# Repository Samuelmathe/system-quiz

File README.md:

# DMX Quiz Project (Arduino + Python)

Ce dossier contient :
- des **sketches Arduino** (`.ino`)
- 2 **logiciels Python** (interfaces GUI) pour piloter/configurer le système via USB (port série)

## Contenu

- **Arduino**
  - `megaf.ino` : sketch pour Arduino MEGA (DMX + logique de jeu ; plus de radio directe, voir `rf_nano_bridge.ino`)
  - `rf_nano_bridge.ino` : sketch pour **RF-Nano** (Nano + nRF24 intégrés) — pont radio nRF24 ↔ série vers le Mega ; seule carte du système avec un module radio
  - `buzzer_nano_equipe.ino` : sketch pour Arduino NANO (équipe)
  - `nano_son_final.ino` : sketch pour Arduino NANO (son)
  - `nano_animateur_final.ino` : sketch pour Arduino NANO (animateur)

- **Python**
  - `configuration/config_final_30.py` : outil de configuration (équipes / DMX / sync MEGA)
  - `interface/interface_30eq.py` : interface “quiz board” (scores/buzz + série)
  - `diagnostics/quiz_logger.py` : logger de diagnostic (écoute passive d'un port série dédié, en parallèle du logiciel de score — voir [Diagnostics](#diagnostics-quiz_loggerpy))

**Modes d’utilisation (sans PC / PC+Mega / PC+nano son)** : voir [MODES.md](MODES.md).

## Prérequis

- Python 3.9+ recommandé
- Arduino IDE (ou PlatformIO) pour compiler/téléverser les `.ino`

## Installation Python

Depuis la racine du projet :

```bash
python3 -m pip install --user -r requirements.txt
```

## Lancer les logiciels Python

Depuis la racine du projet :

```bash
python3 configuration/config_final_30.py
python3 interface/interface_30eq.py
```

## Fichiers créés automatiquement (configs)

- `configuration/config_final_30.py` lit/écrit : `configuration/config_quiz_pro.json`
- `interface/interface_30eq.py` lit/écrit : `interface/quiz_board_config.json`

Ces fichiers JSON sont créés automatiquement **à côté de chaque script**, ce qui rend le projet plus simple à partager et lancer depuis n'importe quel dossier.

## Sons (interface)

`interface/interface_30eq.py` essaie de charger des sons depuis le dossier `sounds/` **à côté du script** :
- `buzz.mp3` (buzz général / fallback)
- `victoire.mp3` (bonne réponse)
- `echec.mp3` (mauvaise réponse)
- `equipe_1.mp3` → `equipe_30.mp3` (sons spécifiques par équipe, optionnels)

Le dossier `sounds/` doit être **à côté du script** (ou à côté de l’exécutable si tu as “packagé” l’app).
Exemple attendu :

```
interface/
  interface_30eq.py
  sounds/
    buzz.mp3
    victoire.mp3
    echec.mp3
    equipe_1.mp3
    ...
    equipe_30.mp3
```

Si `pygame` n’est pas dispo (ou si les fichiers sont absents), l’interface fonctionne, mais sans sons.

## Diagnostics (`quiz_logger.py`)

Outil séparé du logiciel de score : il écoute en **passif** un port série de diagnostic
(un adaptateur USB-TTL dédié, branché en parallèle sur `PC_SERIAL`/`Serial3` du Mega —
aucun conflit avec le logiciel de score, qui utilise son propre adaptateur).

Il affiche le flux en direct, enregistre le log complet dans un fichier horodaté, et
génère un fichier résumé (durée de session, nombre de buzz, freezes/silences détectés,
redémarrages Mega détectés) pratique à partager pour du support/diagnostic à distance.

```bash
python3 diagnostics/quiz_logger.py
```

Un exécutable Windows est aussi généré automatiquement par GitHub Actions à chaque
modification de ce fichier (voir l'onglet *Actions* du dépôt).

## Linux : accès au port série Arduino

Si tu as une erreur de permission sur `/dev/ttyACM0` ou `/dev/ttyUSB0` :

```bash
sudo usermod -aG dialout $USER
```

Puis **déconnexion/reconnexion** (ou redémarrage) pour que le groupe soit pris en compte.

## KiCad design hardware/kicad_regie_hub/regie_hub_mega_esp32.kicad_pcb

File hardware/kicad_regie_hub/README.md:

# Schéma de départ — Régie/Hub (adaptateur Mega + ESP32 + nRF24)

`regie_hub_mega_esp32.kicad_sch` : même méthode que les deux cartes buzzer (généré, **vérifié avec `kicad-cli sch erc` réel**). 11 composants, 14 nets.

## ⚠️ Correction : broches VCC/GND du nRF24 inversées, module PA+LNA (2×4)

Même correction que sur la carte buzzer Nano (voir `../kicad_buzzer_nano/README.md` pour le détail complet) : **J_NRF avait VCC en broche 1 et GND en broche 2 — inversé par rapport à la vraie numérotation** (broche 1 = GND, broche 2 = VCC), vérifié contre 3 sources indépendantes. Corrigé partout. Ton module confirmé étant un **nRF24L01+PA+LNA** (2×4 broches), l'empreinte J_NRF est passée de `PinSocket_1x08` à `PinHeader_2x04` (connecteur **mâle** — le module a lui-même des ports femelles, donc c'est la carte qui doit porter les broches mâles).

## Ce que cette carte est (et n'est pas)

**Ce n'est PAS un shield Mega complet.** Le shield DMX (`quizkicad/mega`, projet séparé, non touché) s'empile déjà directement sur la Mega. Cette carte-ci est un **petit adaptateur** qui porte l'ESP32 + le nRF24 + l'électronique entre les deux, relié à la Mega par seulement **6 fils** :

| Broche J_MEGA | Signal | Vers la Mega |
|---|---|---|
| 1 | TX2 (5V) | Mega pin 16 |
| 2 | RX2 | Mega pin 17 |
| 3 | TX1 (5V) | Mega pin 18 |
| 4 | RX1 | Mega pin 19 |
| 5 | 5V | Sortie régulateur onboard de la Mega |
| 6 | GND | Masse commune |

⚠️ **[FIX] Broches 3/4 déplacées de Mega Serial3 (pins 14/15) vers Mega Serial1 (pins 18/19)** : en vérifiant le câblage réel avec Samuel, Serial3 était déjà utilisé par le shield DMX (mal aiguillé côté firmware, corrigé dans `megaf.ino`) et doit rester dédié au câble TTL PC (scripts Python) comme lien de secours simultané au WiFi. Serial1 était complètement libre sur la Mega — voir `megaf.ino` et `esp32/esp32_bridge_server.ino` pour le détail complet.

**Alimentation** : pas de batterie sur cette carte — confirmé par toi : "on branche le mega [secteur] mais le reste des modules sera alimenté [par lui]". Le 5V vient du régulateur déjà présent sur la Mega.

## Pourquoi un pont diviseur et pas un module convertisseur de niveau logique

Tu as mentionné un "convertisseur logique" entre les RX/TX de la Mega et de l'ESP32. J'ai utilisé le **pont diviseur 1kΩ/2kΩ** à la place d'un module dédié — ce n'est pas un raccourci, c'est la solution **déjà documentée et déjà validée sur ce projet** (`cl.md` section 3.3, schéma dans `docs/APK_HYBRIDE_GUIDE.md`) pour exactement ces deux liaisons série. Réutiliser une solution qui marche déjà coûte moins cher et évite d'introduire une dépendance à un nouveau module non testé sur ce projet.

- **R1/R2** : diviseur sur Mega TX2 (5V) → ESP32 RX1 (3,3V) — lien Jeu.
- **R3/R4** : diviseur sur Mega TX1 (5V) → ESP32 RX2 (3,3V) — lien Config EEPROM (déplacé depuis TX3, voir note ci-dessus).
- **Pas de diviseur dans l'autre sens** (ESP32 TX → Mega RX) : déjà documenté que le 3,3V est lu comme HIGH par les entrées 5V de la Mega, connexion directe.

## Pourquoi un régulateur dédié au nRF24 (pas le 3V3 de l'ESP32)

Demandé : "un régulateur pour esp32" + "tout ce qui va avec ces composants pour un meilleur rendement". Plutôt que d'alimenter le nRF24 depuis la broche 3V3 embarquée de l'ESP32 (qui partage déjà la charge du Wi-Fi — creux de tension possible, cause connue d'instabilité nRF24, historique documenté sur ce projet), **U_REG** est un module régulateur 3,3V dédié rien que pour le nRF24, avec son propre découplage (C2, C3 — le condensateur 10-100µF déjà exigé par `cl.md` pour le nRF24).

## Avertissements ERC (36 au total)

Même profil que les deux cartes buzzer, déjà expliqué en détail dans `../kicad_buzzer_nano/README.md` — normal en pratique KiCad (comparé contre `quizkicad/mega`, ton propre projet fait à la main) :

| Type | Nombre | Normal ? |
|---|---|---|
| `endpoint_off_grid` | 20 | Cosmétique |
| `lib_symbol_mismatch` | 9 | Cosmétique — `Outils > Mettre à jour les symboles depuis la bibliothèque` |
| `pin_not_connected` | 4 | 2 attendus (3V3 onboard ESP32 et IRQ nRF24, non utilisés — no-connect posé), 2 liés au réseau GND (nuance ERC normale, voir README buzzer) |
| `no_connect_dangling` | 2 | Marqueurs "pas de connexion" légèrement décalés — à recaler d'un clic |
| `power_pin_not_driven` | 1 | Normal sur un réseau GND (également présent dans `quizkicad/mega`) |

## PCB : placement compact + pistes routées

`regie_hub_mega_esp32.kicad_pcb` : empreintes placées, **et pistes routées** — même pipeline que les deux cartes buzzer (Freerouting en CLI headless + réimport KiCad + `kicad-cli pcb drc` réel), voir `../kicad_buzzer_nano/README.md` pour le détail (y compris le mécanisme de keepout, identique ici).

**Changements suite à ta relecture** :
- **Le texte-guide en sérigraphie a été retiré** — repères de composants standards uniquement (J_MEGA, U_ESP32L/R, J_NRF, U_REG, R1-R4, C1-C3), pas de paragraphe d'instructions gravé sur la carte.
- **Carte bien plus compacte** : ~137×85mm au lieu de 185×145mm.
- **C3 (découplage nRF24) encore rapproché de J_NRF** (~12mm, contre 25mm dans la toute première version).
- **Zone sans cuivre sous le nRF24** : même mécanisme keepout que la carte Nano (voir son README pour le détail de la vérification), placé en presqu'île contre le bord droit pour ne bloquer aucun chemin de routage.
- **U_ESP32 est un vrai port femelle** : deux barrettes `PinSocket_1x15` (U_ESP32L/R, 30 broches, entraxe 15,24mm). Seules 11 des 30 positions physiques sont câblées ; les 19 autres sont présentes pour que le module s'enfiche mécaniquement. Brochage : **DOIT ESP32 DevKit V1, 30 broches** — exactement le modèle confirmé commandé, design de référence unique et bien plus standardisé que les clones 38 broches (vérifié sur https://www.espboards.dev/esp32/esp32doit-devkit-v1/).
- **J_NRF (nRF24) est un connecteur MÂLE 2×4** (`PinHeader_2x04`) — le module a des ports femelles dessus, donc la carte porte les broches mâles. 1=GND, 2=VCC, puis CE/CSN/SCK/MOSI/MISO/IRQ. ⚠️ **Vérifie les repères sur ton module avant de souder**, aucun standard universel pour les variantes PA+LNA.
- **R1-R4 et C1-C3 sont maintenant en CMS** (`R_0805`/`C_0805`), par choix explicite pour un assemblage machine (PCBA) chez le fabricant. Même numérotation de broche qu'avant. **Restent traversants** : J_MEGA, U_ESP32L/R et J_NRF (connecteurs de liaison/modules enfichables, pas adaptés au CMS).
- Aperçu : `apercu_pcb.png`.

**Résultat** : 78 connexions (14 nets), **0 violation de clearance, 0 élément non connecté**, 5 vias placées, keepout respecté (0 piste dedans, vérifié par script). DRC final : 12 avertissements, tous `lib_footprint_mismatch` (cosmétique). 4 `track_dangling` initiaux (résidus d'autorouter) identifiés et supprimés après vérification de la topologie réelle — **0 track_dangling restant**.

**C3 (découplage nRF24) rapproché de J_NRF** : le placement initial mettait C3 à 25mm de J_NRF (net `NRF_VCC_DEDIE`, qui relie aussi C2 et U_REG — ce n'est pas un simple lien à 2 broches). Trop loin pour un découplage propre à 2,4GHz. C3 a été repositionné à 12mm de J_NRF (`(152,20)` au lieu de `(165,20)`) et la carte entièrement re-routée : la piste J_NRF↔C3 est maintenant un tronçon direct et court, visible sur `apercu_pcb.png`.

## Prochaine étape

Ouvre le PCB dans KiCad et relis le routage à l'œil, puis passe aux fichiers de fabrication (Gerbers) — en particulier bien respecter les recommandations `cl.md` (VCC nRF24 en 3,3V uniquement jamais 5V, GND commun).

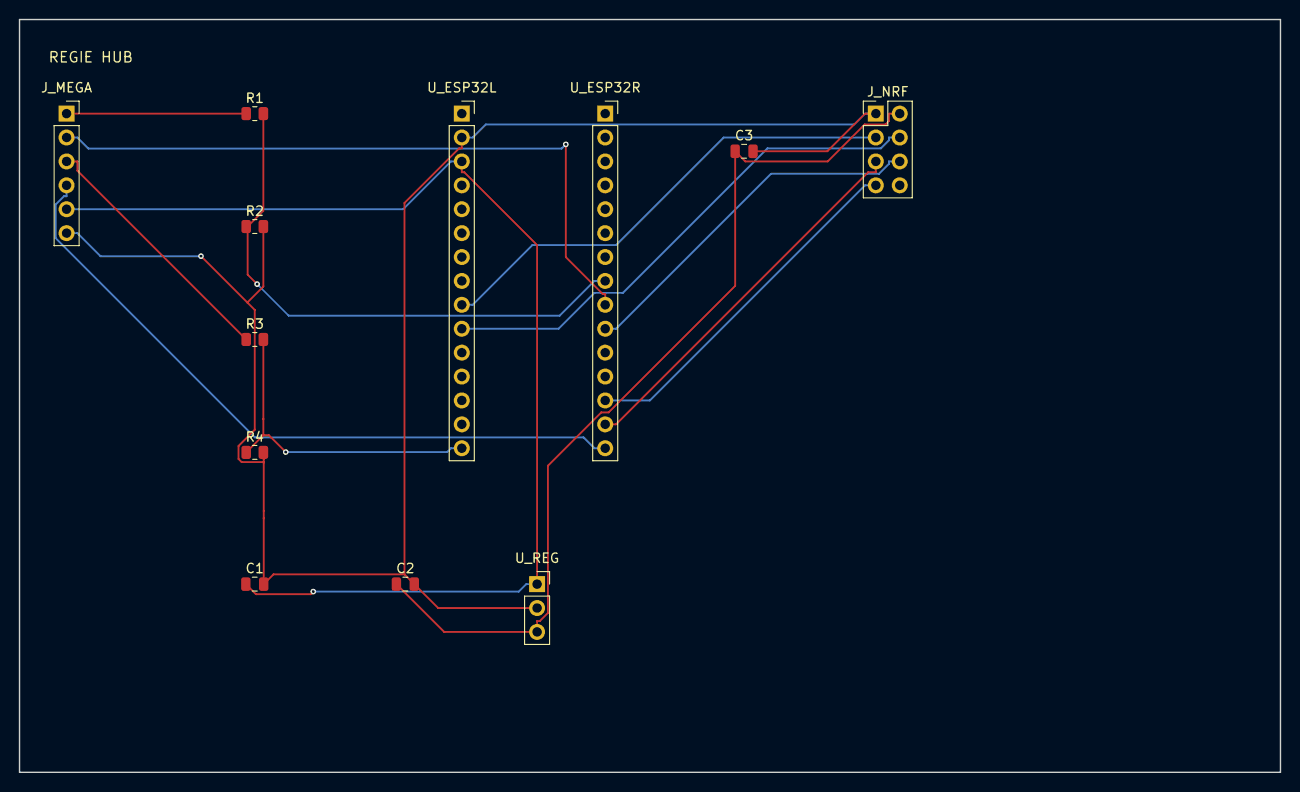
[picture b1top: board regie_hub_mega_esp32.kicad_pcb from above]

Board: 2 copper layers, 134.0 x 80.0 mm, 12 parts (0 on the bottom side), 14 nets.

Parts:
C1: ~10uF decouplage entree regulateur - CMS; C_0805_2012Metric
C2: ~10uF decouplage sortie regulateur - CMS; C_0805_2012Metric
C3: 10-100uF decouplage nRF24 (obligatoire, au plus p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; C_0805_2012Metric
J_MEGA: Vers Mega: TX2(16) RX2(17) TX1(18) RX1(19) 5V GND; PinSocket_1x06_P2.54mm_Vertical
J_NRF: nRF24L01+PA+LNA (broches MALES, le module a des p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; PinHeader_2x04_P2.54mm_Vertical
R1: 1k (diviseur TX2, serie) - CMS; R_0805_2012Metric
R2: 2k (diviseur TX2, vers GND) - CMS; R_0805_2012Metric
R3: 1k (diviseur TX3, serie) - CMS; R_0805_2012Metric
R4: 2k (diviseur TX3, vers GND) - CMS; R_0805_2012Metric
U_ESP32L: ESP32 DevKit V1 colonne gauche (broches 1-15); PinSocket_1x15_P2.54mm_Vertical
U_ESP32R: ESP32 DevKit V1 colonne droite (broches 16-30); PinSocket_1x15_P2.54mm_Vertical
U_REG: Regulateur 3.3V dedie (ex AMS1117-3.3); PinSocket_1x03_P2.54mm_Vertical

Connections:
ESP32_RX1_3V3: R1.2, R2.1, U_ESP32R.23
ESP32_RX2_3V3: R3.2, R4.1, U_ESP32L.15
GND: C1.2, C2.2, C3.2, J_MEGA.6, J_NRF.1, R2.2, R4.2, U_ESP32L.2, U_REG.2
MEGA_RX2_DIRECT: J_MEGA.2, U_ESP32R.22
MEGA_RX3_DIRECT: J_MEGA.4, U_ESP32R.16
MEGA_TX2_5V: J_MEGA.1, R1.1
MEGA_TX3_5V: J_MEGA.3, R3.1
NRF_CE: J_NRF.3, U_ESP32L.9
NRF_CSN: J_NRF.4, U_ESP32L.10
NRF_MISO: J_NRF.7, U_ESP32R.18
NRF_MOSI: J_NRF.6, U_ESP32R.21
NRF_SCK: J_NRF.5, U_ESP32R.17
NRF_VCC_DEDIE: C2.1, C3.1, J_NRF.2, U_REG.3
VCC_5V_MEGA: C1.1, J_MEGA.5, U_ESP32L.3, U_REG.1

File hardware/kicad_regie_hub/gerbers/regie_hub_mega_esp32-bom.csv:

Designator,Comment,Footprint
C1,~10uF decouplage entree regulateur - CMS,Capacitor_SMD:C_0805_2012Metric
C2,~10uF decouplage sortie regulateur - CMS,Capacitor_SMD:C_0805_2012Metric
C3,"10-100uF decouplage nRF24 (obligatoire, au plus pres) - CMS",Capacitor_SMD:C_0805_2012Metric
J_MEGA,Vers Mega: TX2 RX2 TX3 RX3 5V GND,Connector_PinSocket_2.54mm:PinSocket_1x06_P2.54mm_Vertical
J_NRF,"nRF24L01+PA+LNA (broches MALES, le module a des ports femelles) - VERIFIER le brochage sur le module recu",Connector_PinHeader_2.54mm:PinHeader_2x04_P2.54mm_Vertical
R1,"1k (diviseur TX2, serie) - CMS",Resistor_SMD:R_0805_2012Metric
R2,"2k (diviseur TX2, vers GND) - CMS",Resistor_SMD:R_0805_2012Metric
R3,"1k (diviseur TX3, serie) - CMS",Resistor_SMD:R_0805_2012Metric
R4,"2k (diviseur TX3, vers GND) - CMS",Resistor_SMD:R_0805_2012Metric
U_ESP32L,ESP32 DevKit V1 colonne gauche (broches 1-15),Connector_PinSocket_2.54mm:PinSocket_1x15_P2.54mm_Vertical
U_ESP32R,ESP32 DevKit V1 colonne droite (broches 16-30),Connector_PinSocket_2.54mm:PinSocket_1x15_P2.54mm_Vertical
U_REG,Regulateur 3.3V dedie (ex AMS1117-3.3),Connector_PinSocket_2.54mm:PinSocket_1x03_P2.54mm_Vertical

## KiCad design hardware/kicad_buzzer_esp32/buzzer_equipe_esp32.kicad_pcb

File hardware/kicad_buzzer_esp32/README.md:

# Schéma de départ — Buzzer équipe (secours ESP32 / ESP-NOW)

`buzzer_equipe_esp32.kicad_sch` : même méthode que `../kicad_buzzer_nano/` (généré à partir du BOM, vérifié avec `kicad-cli sch erc` réel). 6 composants, 6 nets.

## L'ESP32 est représenté comme un connecteur générique 4 broches

Il n'existe pas de symbole KiCad standard pour la carte exacte commandée (ESP32 DevKit V1/ESP32-DevKitC-32 — trop de variantes de brochage différentes selon les fabricants). **U1** représente donc uniquement les 4 signaux réellement câblés sur ce PCB vers le module ESP32, pas les ~30 broches physiques :

| Broche U1 | Signal ESP32 | Usage (voir `esp32_buzzer_equipe.ino`) |
|---|---|---|
| 1 | GPIO4 | Bouton buzz |
| 2 | GPIO13 | IN du module vibreur |
| 3 | 5V / VIN | Alimentation |
| 4 | GND | Masse |

GPIO2 (LED embarquée) n'apparaît pas : elle est **interne au module ESP32 lui-même**, rien à router sur ce PCB pour elle.

## Avertissements ERC (28 au total)

| Type | Nombre | Normal ? |
|---|---|---|
| `endpoint_off_grid` | 12 | Cosmétique, sans conséquence électrique |
| `pin_not_connected` | 7 | À vérifier une fois dans l'interface — voir note ci-dessous |
| `lib_symbol_mismatch` | 7 | Cosmétique — `Outils > Mettre à jour les symboles depuis la bibliothèque` |
| `label_dangling` | 1 | **Normal en pratique** — ton propre projet `quizkicad/mega` (fait à la main) en a **71** du même genre. Pas un signe d'erreur de génération. |
| `power_pin_not_driven` | 1 | **Normal en pratique** — présent aussi dans `quizkicad/mega` (3 occurrences). |

Le `label_dangling` et plusieurs `pin_not_connected` concernent le réseau `BAT_PLUS`/`GND` autour de `BT1`/`J2`/`U1` — les coordonnées calculées correspondent bien aux broches réelles (vérifié), mais KiCad les affiche quand même comme non connectés. Comme pour la version Nano : cliquez l'étiquette et redéplacez-la légèrement pour forcer la reconnexion visuelle, ou ignorez si vous câblez de toute façon ce réseau en dur au routage du PCB.

## Rappel important

`ESPNOW_WIFI_CHANNEL` dans `esp32_buzzer_equipe.ino` doit rester identique à celui du hub (`esp32/esp32_bridge_server.ino`) — sans rapport avec ce schéma, mais à ne pas oublier au premier flash de la carte.

## PCB : placement compact + pistes routées

`buzzer_equipe_esp32.kicad_pcb` : empreintes placées, **et pistes routées** — même pipeline que la carte Nano (Freerouting en CLI headless + réimport KiCad + `kicad-cli pcb drc` réel), voir `../kicad_buzzer_nano/README.md` pour le détail du pipeline.

**Changements suite à ta relecture** :
- **Le texte-guide en sérigraphie a été retiré** — repères de composants standards uniquement (U1L, U1R, SW1...).
- **Carte bien plus compacte** : ~68×101mm au lieu de 130×145mm.
- **v3 : réduite encore à 65×50mm exactement**, pour correspondre au boîtier déjà conçu. U1L/U1R (les deux barrettes du module ESP32, 49mm de long chacune) ont dû être **pivotées à 90°** pour tenir dans cette largeur — leur entraxe réel (22,86mm) est inchangé, seule l'orientation sur la carte change, ça ne modifie rien au câblage ni au module qui s'enfiche dessus. Les 6 petits connecteurs (SW1, SW2, BATLED, J3, J2, BT1) sont serrés sur une seule rangée en bas de la carte, J2/J3 également pivotés à 90° pour gagner de la place en hauteur.
- Pas de keepout sur cette carte : pas de nRF24 ici, l'ESP-NOW utilise l'antenne intégrée à la puce ESP32 elle-même.
- **SW1, SW2, J2, J3 (connecteurs "fils volants") sont maintenant en CMS** (empreintes SMD), par choix explicite pour un assemblage machine (PCBA) chez le fabricant. Même numérotation de broche qu'avant. **Restent traversants** : U1L/U1R (le module ESP32 s'enfiche dessus) et **BT1**.
- **BT1 (batterie) est un vrai connecteur JST-PH** (`JST_PH_B2B-PH-K`, mâle, traversant) — même raisonnement que la carte Nano (voir son README) : la batterie a déjà une prise femelle sertie sur ses fils, et ce connecteur encaisse des cycles de branchement/débranchement qu'un pad CMS ne supporterait pas. Broche 1 = + (rouge), broche 2 = − (noir) — **vérifie la polarité sur ta batterie reçue**.
- **Nouveau : BATLED**, connecteur 2 broches (CMS) pour le module indicateur de niveau de batterie (4 LED) — même composant/câblage que la carte Nano, voir son README pour le détail.

**U1 est un vrai port femelle** : deux barrettes `PinSocket_1x19` (U1L/U1R, 38 broches au total, entraxe 22,86mm — la dimension déjà notée dans `hardware/boitier_buzzer_equipe.scad` pour ce module). Seules 4 des 38 positions physiques sont câblées (GPIO4, GPIO13, VIN, GND) ; les 34 autres sont présentes uniquement pour que le module s'enfiche mécaniquement.

⚠️ **Brochage à vérifier sur le module reçu avant de souder** : contrairement à la carte hub (ESP32 DevKit V1 30 broches, un modèle de référence unique et confirmé par toi), les cartes ESP32 38 broches existent en plusieurs variantes de brochage chez différents fabricants. J'ai utilisé la disposition générique la plus courante ("style NodeMCU-32S", vérifiée sur https://www.espboards.dev/esp32/esp32-38pin-devkit-generic/) : broche réelle 32 = GPIO4, broche 15 = GPIO13, broche 19 = VIN, broche 14 = GND. **Compare ces numéros avec les repères imprimés sur ton module avant de souder** — si ça ne correspond pas, il suffit de déplacer les 4 fils, la carte elle-même n'a pas besoin d'être refaite.

- Aperçu : `apercu_pcb.png`.

**Résultat (v3, 65×50mm)** : **0 violation de clearance, 0 élément non connecté**. DRC final : 19 avertissements, tous cosmétiques — `lib_footprint_mismatch` (5, comme d'habitude), `silk_overlap` (1, texte de référence U1R qui chevauche légèrement son propre contour après la rotation à 90°), et `silk_over_copper` (13, des pistes routées passent juste sous la sérigraphie de J2/J3 — carte très dense, aucun impact électrique, juste un risque que l'encre sérigraphie ne s'imprime pas parfaitement à ces endroits précis). Un `track_dangling` initial (résidu d'autorouter, un stub B.Cu redondant en doublon d'un chemin déjà assuré côté F.Cu) identifié et supprimé après vérification de la topologie réelle — **0 track_dangling restant**.

## Prochaine étape

Ouvre le PCB dans KiCad, relis le routage à l'œil, puis passe aux fichiers de fabrication (Gerbers).

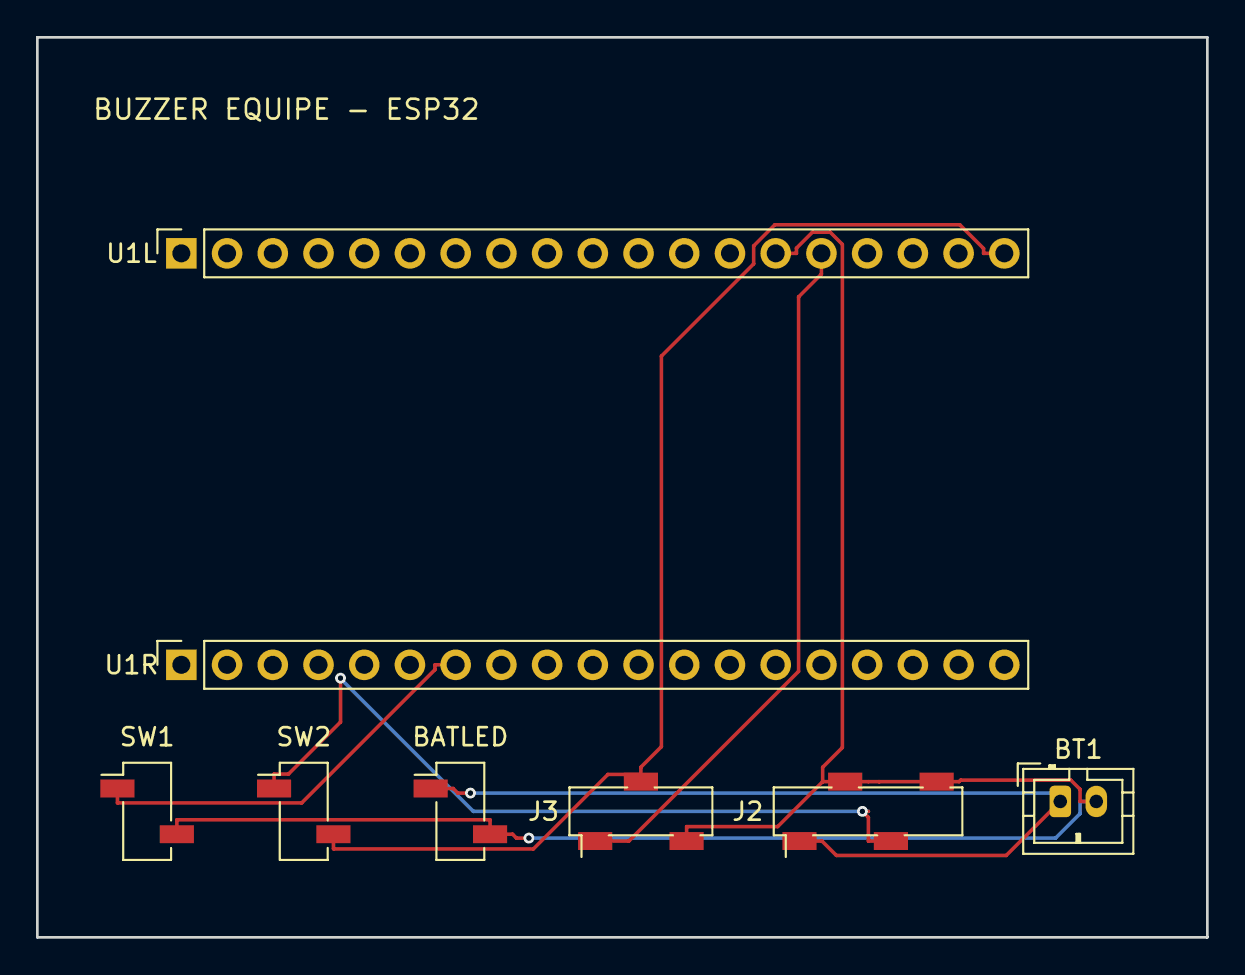
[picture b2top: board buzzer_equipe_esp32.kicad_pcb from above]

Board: 2 copper layers, 65.0 x 50.0 mm, 8 parts (0 on the bottom side), 6 nets.

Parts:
BATLED: Indicateur niveau batterie (4 LED) - CMS - 1=B+ 2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; PinSocket_1x02_P2.54mm_Vertical_SMD_Pin1Left
BT1: Batterie LiPo 1S 1000-1200mAh - connecteur JST-PH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; JST_PH_B2B-PH-K_1x02_P2.00mm_Vertical
J2: Module charge TP4056+protect+boost USB-C - CMS; PinSocket_1x04_P2.54mm_Vertical_SMD_Pin1Left
J3: Module vibreur IN/VCC/GND - CMS; PinSocket_1x03_P2.54mm_Vertical_SMD_Pin1Left
SW1: Bouton BUZZ (fils volants) - CMS; PinSocket_1x02_P2.54mm_Vertical_SMD_Pin1Left
SW2: Interrupteur marche/arret (fils volants) - CMS; PinSocket_1x02_P2.54mm_Vertical_SMD_Pin1Left
U1L: ESP32 colonne gauche (broches 1-19) - VERIFIER su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; PinSocket_1x19_P2.54mm_Vertical
U1R: ESP32 colonne droite (broches 20-38) - VERIFIER s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; PinSocket_1x19_P2.54mm_Vertical

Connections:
BAT_PLUS: BATLED.1, BT1.1, J2.1
BTN_SIG: SW1.1, U1R.32
GND: BATLED.2, BT1.2, J2.2, J2.4, J3.3, SW1.2, U1L.14
VCC_5V_RAW: J2.3, SW2.1
VCC_5V_SW: J3.2, SW2.2, U1L.19
VIBE_IN: J3.1, U1L.15

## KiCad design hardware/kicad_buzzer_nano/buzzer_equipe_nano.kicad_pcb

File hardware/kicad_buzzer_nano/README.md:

# Schéma de départ — Buzzer équipe (Nano + nRF24)

`buzzer_equipe_nano.kicad_sch` : schéma généré à partir du BOM (`../../docs/BOM_BUZZER_EQUIPE.md`), **vérifié avec KiCad lui-même** (`kicad-cli sch erc`, format v9.0) — pas juste du texte non testé. 8 composants, 12 nets connectés (alimentation, bouton, module vibreur, nRF24 sur SPI matériel).

## ⚠️ Correction : broches VCC/GND du nRF24 inversées dans une version précédente

En répondant à ta question "le nrf24 c'est sur une ligne ?", j'ai vérifié le brochage du module nRF24 contre 3 sources indépendantes (components101.com, lastminuteengineers.com, doc générale nRF24L01+) et découvert que **J1 avait VCC en broche 1 et GND en broche 2 — c'est l'inverse** de la vraie numérotation (broche 1 = GND, broche 2 = VCC ; la broche 1 est d'ailleurs toujours la pastille carrée sur cette empreinte, et GND est documenté comme "identifiable par son marquage carré" sur les vrais modules). Corrigé partout : schéma, PCB, ce README. Si tu avais déjà commencé à câbler en suivant l'ancienne version, vérifie/corrige avant de mettre sous tension.

Tu as aussi confirmé que ton module est un **nRF24L01+PA+LNA** (longue portée, antenne externe) — ses 8 broches sont sur un connecteur **2×4**, pas 1×8 comme le module standard. L'empreinte J1 a été changée en conséquence (voir section PCB ci-dessous).

## Comment l'ouvrir

Ouvrez `buzzer_equipe_nano.kicad_sch` directement dans KiCad (File > Open). Aucun `.kicad_pro` fourni — KiCad vous proposera d'en créer un, acceptez.

## À faire en premier en l'ouvrant

L'ERC (`Inspecter > Vérification des règles électriques`) remonte 72 avertissements. La plupart sont normaux, mais trois méritent un coup d'œil :

| Avertissement | Nombre | À faire |
|---|---|---|
| `pin_not_connected` | 30 | **Normal** — la plupart des broches du Nano (A0-A7, D0/D1/D3/D4/D6/D7/D8...) ne sont pas utilisées par ce boîtier. Ignorer, ou ajouter des drapeaux "Pas de connexion" si vous voulez un ERC propre. |
| `lib_symbol_mismatch` | 12 | Cosmétique — mes copies embarquées des symboles (GND, +3V3, Battery_Cell) diffèrent légèrement de la bibliothèque système. `Outils > Mettre à jour les symboles depuis la bibliothèque` règle ça en un clic. |
| `endpoint_off_grid` | 19 | Cosmétique — mes coordonnées calculées ne tombent pas toujours pile sur la grille par défaut de KiCad. Sans conséquence électrique, juste esthétique. |
| `label_dangling` | 3 | **Normal en pratique** — `BAT_PLUS`, `NRF_SCK`, `VCC_5V_SW` : l'étiquette semble pile sur la bonne broche (vérifié par calcul), KiCad la signale quand même comme non connectée. J'ai vérifié : **ton propre projet `quizkicad/mega`** (fait à la main dans KiCad, pas généré) a **71** avertissements du même genre — c'est une nuance ERC courante, pas un signe d'erreur de génération. Cliquez l'étiquette et redéplacez-la légèrement si vous voulez un ERC propre, sinon ignorez. |
| `no_connect_dangling` | 1 | Le marqueur "pas de connexion" sur la broche IRQ du module nRF24 (non utilisée par le firmware) est légèrement décalé — à recaler d'un clic sur la broche. |
| `power_pin_not_driven` / `pin_not_driven` | 4 + 3 | Également présent dans `quizkicad/mega` (3 occurrences de `power_pin_not_driven`) — nuance ERC normale sur les réseaux GND, pas un bug. |

## PCB : placement compact + pistes routées

`buzzer_equipe_nano.kicad_pcb` : empreintes placées, **et pistes routées** — 2 couches (F.Cu/B.Cu), autoroutées avec [Freerouting](https://freerouting.app/) (outil open source dédié, pas un routage "deviné" à la main par moi) puis réimportées dans KiCad, le tout vérifié avec `kicad-cli pcb drc` réel.

**Changements suite à ta relecture** :
- **Le texte-guide en sérigraphie a été retiré** — ça n'a pas sa place gravé sur un vrai circuit fabriqué. Il ne reste que les repères de composants standards (A1L, J1, C1...), comme sur n'importe quelle carte.
- **Carte bien plus compacte** : ~90×100mm au lieu de 125×145mm — composants resserrés, plus d'espace perdu.
- **C1 (découplage nRF24) déplacé juste à côté de J1** (~10-12mm au lieu de ~30mm) pour un découplage propre.
- **Zone sans cuivre sous le nRF24** : un keepout (pistes/vias/plans interdits, sur les deux couches F.Cu et B.Cu) couvre l'espace où le corps/l'antenne du module PA+LNA se trouve une fois enfiché — pour ne pas mettre de cuivre sous l'antenne. Positionné en "presqu'île" contre le bord droit de la carte (rien ne route à travers), pas collé sur J1 des deux côtés — une première tentative avait bloqué le routeur (8 pistes bloquées après 100+ passes) en enfermant le connecteur ; corrigé en laissant un côté totalement ouvert. **Vérifié réellement respecté par Freerouting** (pas juste accepté par KiCad) via un test dédié où un keepout bloquant délibérément le seul chemin entre 2 pastilles a fait router 0 piste par l'autorouteur — preuve qu'il n'était pas ignoré. Taille/position à vérifier/ajuster dans KiCad selon les dimensions réelles de ton module.
- **Le Nano est représenté par de vrais ports femelles** : deux barrettes `PinSocket_1x15` séparées (A1L = broches réelles 1-15, A1R = 16-30, espacées de 15,24mm comme sur un vrai Nano). Le Nano s'enfiche dessus, rien à souder sur le module lui-même.
- **J1 (nRF24) est un connecteur MÂLE 2×4** (`PinHeader_2x04`) — corrigé après que tu as précisé que le module lui-même a des ports femelles dessus, donc c'est la carte qui doit porter des broches mâles pour que le module s'enfiche dessus (logique inverse de A1L/A1R où c'est le Nano qui a des broches mâles). Broches 1=GND et 2=VCC sur la 1ère rangée, puis CE/CSN, SCK/MOSI, MISO/IRQ — ordre le plus souvent publié pour ce type de module, mais **aucun standard universel n'existe pour les variantes PA+LNA**. ⚠️ **Vérifie les repères imprimés sur ton module avant de souder.**
- **C1 et les connecteurs "fils volants" (SW1, SW2, J2, J3) sont maintenant en CMS** (empreintes SMD — `C_0805`, `PinSocket_..._SMD`), par choix explicite pour un assemblage machine (PCBA) chez le fabricant plutôt qu'à souder toi-même. Même numérotation de broche que les anciennes versions traversantes, rien d'autre n'a changé côté câblage. **Restent traversants** : A1L/A1R (Nano), J1 (nRF24) — headers de modules enfichables, pas adaptés au CMS — et **BT1**, voir point suivant.
- **BT1 (batterie) est maintenant un vrai connecteur JST-PH** (`JST_PH_B2B-PH-K`, mâle, traversant) au lieu de simples pastilles. Les batteries LiPo standards arrivent avec une prise JST-PH **femelle** déjà sertie sur leurs fils — la batterie se branche donc directement, rien à couper ni souder sur ses fils. Volontairement resté traversant (pas de version CMS) : ce connecteur encaisse des cycles répétés de branchement/débranchement, un pad CMS se décollerait à l'usage. Broche 1 = + (fil rouge), broche 2 = − (fil noir) — convention quasi universelle sur les batteries LiPo JST-PH, mais **vérifie la polarité sur ta batterie reçue** avant de brancher.
- **Nouveau : BATLED**, connecteur 2 broches (CMS) pour le module indicateur de niveau de batterie (4 LED, 25/50/75/100% — module "1S lithium battery capacity indicator", vérifié via handsontec.com). Branché directement en parallèle sur la batterie (même net que BT1 : broche 1 = B+, broche 2 = B-, ~5mA, toujours actif, pas de bouton). Voir `../../docs/BOM_BUZZER_EQUIPE.md`.
- Aperçu : `apercu_pcb.png`.

**Pipeline utilisé** : `pcbnew.ExportSpecctraDSN()` → `freerouting.jar` (mode CLI headless, `-mp 20`) → `pcbnew.ImportSpecctraSES()` → `kicad-cli pcb drc`. 74 connexions, **0 violation de clearance, 0 élément non connecté**, keepout respecté (0 piste dedans, vérifié par script).

**DRC final** : 5 avertissements, tous `lib_footprint_mismatch` (cosmétique, se corrige avec `Outils > Mettre à jour les empreintes depuis la bibliothèque`) — **0 track_dangling** dès le premier autoroutage cette fois.

**À vérifier toi-même avant fabrication** : largeur de piste/clearance par défaut de KiCad (pas de netclass personnalisée définie ici) — correcte pour du signal logique, mais à confirmer sur les nets d'alimentation (`VCC_5V_SW`, `GND`) selon le courant réel du vibreur.

## Prochaine étape

Ouvre `buzzer_equipe_nano.kicad_pcb` dans KiCad et relis le routage à l'œil (largeurs de piste, trajets) avant de passer aux fichiers de fabrication (Gerbers).

La version ESP32 (secours équipe) est dans `../kicad_buzzer_esp32/`, même méthode.

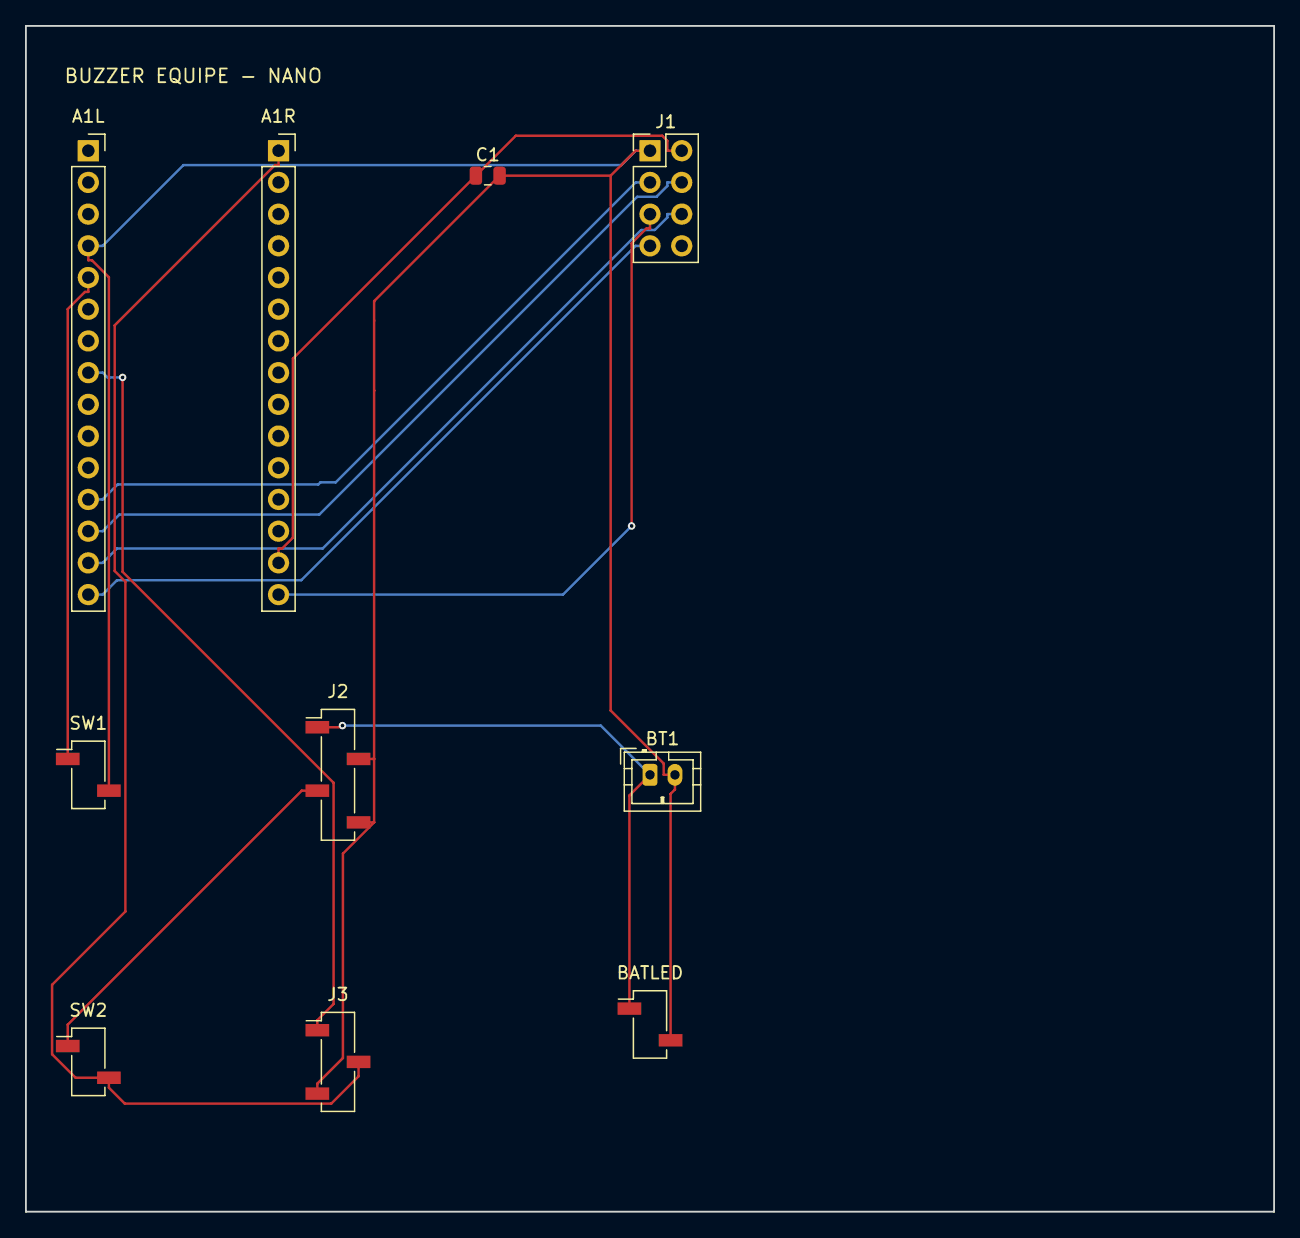
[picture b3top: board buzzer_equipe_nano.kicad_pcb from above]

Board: 2 copper layers, 100.0 x 95.0 mm, 10 parts (0 on the bottom side), 12 nets.

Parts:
A1L: Nano colonne gauche (broches 1-15); PinSocket_1x15_P2.54mm_Vertical
A1R: Nano colonne droite (broches 16-30); PinSocket_1x15_P2.54mm_Vertical
BATLED: Indicateur niveau batterie (4 LED) - CMS - 1=B+ 2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; PinSocket_1x02_P2.54mm_Vertical_SMD_Pin1Left
BT1: Batterie LiPo 1S 500-600mAh - connecteur JST-PH (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; JST_PH_B2B-PH-K_1x02_P2.00mm_Vertical
C1: 10-100uF decouplage nRF24 (obligatoire, au plus p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; C_0805_2012Metric
J1: nRF24L01+PA+LNA (broches MALES, le module a des p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; PinHeader_2x04_P2.54mm_Vertical
J2: Module charge TP4056+protect+boost USB-C - CMS; PinSocket_1x04_P2.54mm_Vertical_SMD_Pin1Left
J3: Module vibreur IN/VCC/GND - CMS; PinSocket_1x03_P2.54mm_Vertical_SMD_Pin1Left
SW1: Bouton BUZZ (fils volants) - CMS; PinSocket_1x02_P2.54mm_Vertical_SMD_Pin1Left
SW2: Interrupteur marche/arret (fils volants) - CMS; PinSocket_1x02_P2.54mm_Vertical_SMD_Pin1Left

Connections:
+3V3: A1R.17, C1.1, J1.2
BAT_PLUS: BATLED.1, BT1.1, J2.1
BTN_SIG: A1L.5, SW1.1
GND: A1L.4, BATLED.2, BT1.2, C1.2, J1.1, J2.2, J2.4, J3.3, SW1.2
NRF_CE: A1L.12, J1.3
NRF_CSN: A1L.13, J1.4
NRF_MISO: A1L.15, J1.7
NRF_MOSI: A1L.14, J1.6
NRF_SCK: A1R.16, J1.5
VCC_5V_RAW: J2.3, SW2.1
VCC_5V_SW: A1R.30, J3.2, SW2.2
VIBE_IN: A1L.8, J3.1

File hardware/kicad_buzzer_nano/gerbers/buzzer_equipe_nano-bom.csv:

Designator,Comment,Footprint
A1L,Nano colonne gauche (broches 1-15),Connector_PinSocket_2.54mm:PinSocket_1x15_P2.54mm_Vertical
A1R,Nano colonne droite (broches 16-30),Connector_PinSocket_2.54mm:PinSocket_1x15_P2.54mm_Vertical
BATLED,Indicateur niveau batterie (4 LED) - CMS - 1=B+ 2=B-,Connector_PinSocket_2.54mm:PinSocket_1x02_P2.54mm_Vertical_SMD_Pin1Left
BT1,Batterie LiPo 1S 500-600mAh - connecteur JST-PH (1=+ 2=-),Connector_JST:JST_PH_B2B-PH-K_1x02_P2.00mm_Vertical
C1,"10-100uF decouplage nRF24 (obligatoire, au plus pres) - CMS",Capacitor_SMD:C_0805_2012Metric
J1,"nRF24L01+PA+LNA (broches MALES, le module a des ports femelles) - VERIFIER le brochage sur le module recu",Connector_PinHeader_2.54mm:PinHeader_2x04_P2.54mm_Vertical
J2,Module charge TP4056+protect+boost USB-C - CMS,Connector_PinSocket_2.54mm:PinSocket_1x04_P2.54mm_Vertical_SMD_Pin1Left
J3,Module vibreur IN/VCC/GND - CMS,Connector_PinSocket_2.54mm:PinSocket_1x03_P2.54mm_Vertical_SMD_Pin1Left
SW1,Bouton BUZZ (fils volants) - CMS,Connector_PinSocket_2.54mm:PinSocket_1x02_P2.54mm_Vertical_SMD_Pin1Left
SW2,Interrupteur marche/arret (fils volants) - CMS,Connector_PinSocket_2.54mm:PinSocket_1x02_P2.54mm_Vertical_SMD_Pin1Left

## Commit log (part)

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2026-05-09 Update sounds documentation
2026-05-09 Improve sounds bundling in CI
2026-05-09 Maximize RF reliability (AutoAck/CRC16/seq/watchdog)
2026-05-09 Apply score app icon from assets/ and bundle in CI
2026-05-09 Add Windows exe icon (score.ico) and CI icon
2026-05-14 mise a jour
2026-05-14 Update sound payload handling and configuration adjustments
2026-05-14 Doc modes, fix DF playMp3Folder, interface nano/score, fiabilité radio
